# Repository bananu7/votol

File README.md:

# bananu7/Votol
Hello. This is my repository for all things related to the Votol controllers I was able to gather and put together.

## My use case and context

I'm converting a CRF250 MX motorcycle to electric power, using the Votol EM260SGTP controller. I want to have a bit more control over it that usual, so I decided to learn more about it.
Unless otherwise noted, all descriptions, labels etc. apply to _my specific controller_. Different models of the controller can differ; make sure you understand the cable functions
and model of yours.

## Project structure

* `desktop/` - early beginnings of a desktop app that were meant to replace the original desktop programmer
* `embassy/` - firmware of the display controller that goes on the bike and communicates with Votol EM
* `reference/` - technical details and descriptions of the controller protocol

## Log

### 2025-02-18

I did some more work on the miscellaneous features for the display. Got better frame decoding working, modularized things and importantly created a simulation mode that allows development without a controller connected (still on real hardware, though). I'm still not sure how I want to present all the available data or what peripherals to connect. Ideas list includes:

* all main controller parameters (works for now: battery voltage, temperatures)
* ride mode
* all controller errors in readable format
* temperature alerts
* speed based on the RPM counter
* trip computer: speed * time (distance traveled), current * time (amp-hours used), max/avg speed, max/avg current, moving time

Additional features based on peripheral hw:
* RTC - clock :), configuration (maybe I could use internal RTC)
* SD or flash - datalogger (trip computer but as series)
* IMU, magnetometer - compass, lean-aware TC
* front wheel speed sensor - TC, more accurate speed
* GPS - time, datalogging position
* BT - phone app, remote config and data reading

This is just a mental note to myself; it's unlikely I'll get to doing all of the above. Once I get the basic features working, I'll also upload the CAD files for the enclosure and print a prototype.

### 2025-02-13

I should've started this log immediately, but better late than never. I have already done quite a lot of work, but a lot still remains to be done.
Dealing with the controller can roughly be grouped into two categories:

1) Programming - setting up current and voltage limits, throttle rampup, engine phase config and hall config, as well as pin functions
2) Using - happens in the vehicle

#### Programming

Programming by itself is reasonably straighforward. I need to write more about the programming setup in the reference section, but in short,
the controller comes with a programming USB dongle. This dongle plugs into a two-pin port on the controller colored blue and orange. In my case,
the two-pin interface is a 1M CAN bus, xceived using TJA1050, connecting to an STM microcontroller, then exposed to USB via an USB-to-serial converter.

The controller also comes with a desktop app that looks like it was written with MFC. The app seems to have been made for older, smaller controllers,
and in fact doesn't even show the 260 on the list. To communicate, it opens a serial port at either 9600 or 115200 baud. There's also the CAN
switch that in my case needed to be... disabled. I believe that it's mostly a consequence of historical debt and reuse. The app originally
talked to the controller via serial; once they switched to CAN they were limited to 8-byte data frames, so they added the intermediate translator
chip to the dongle, so that the old app can still talk to the new controller. Incidentally I've noticed that the serial data going back to the app
is 24 bytes long, while the controller only responds with two can frames - so the translator chip must be doing some shuffling and filling in the 
blanks.

I have recorded some of the programming transactions, but haven't saved them. In order to properly reverse engineer the protocol, a whole
communication scheme needs to be observed and the parameters isolated. That being said, as the app seems to work fine for now, this is of low
priority. Perhaps one exciting possibility here would be to replace it with a web-based version talking serial over WebUSB. That would be a massive
usability boost, but getting all controllers working correctly could be a challenge.

#### Using the controller

Much more interesting is what happens during use. I don't want to use the dongle, and CAN is actually a great interface for the vehicle use.
The displays normally utilized with this controller use the separate LIN output, but I see zero reason to do that. CAN is more robust and offers
much more functionality.

The controller exposes a lot of frames on the bus, none of which I've decoded yet. There's been some mentions from SIA that they're their internal
protocol, but nothing concrete about it. I wouldd assume the usual parameters would be broadcasted continously, which would be great for display
purposes.

At the same time, when the desktop app wants live data from the controller, it sends a special query packet. The controller "responds" by sending
two frames containing the vitals; they are described in the reference folder. I was able to successfully read and decode those frames, and
that's the current state in the `embassy` folder; operating on an STM32F103C8 microcontroller, using its onboard CAN controller and TJA1050 
transceiver. On the other end, I plugged in a simple 8x8x4 LED matrix controlled by four MAX7219 chips in series, over SPI. Works great and 
the display of basic parameters has already been achieved.

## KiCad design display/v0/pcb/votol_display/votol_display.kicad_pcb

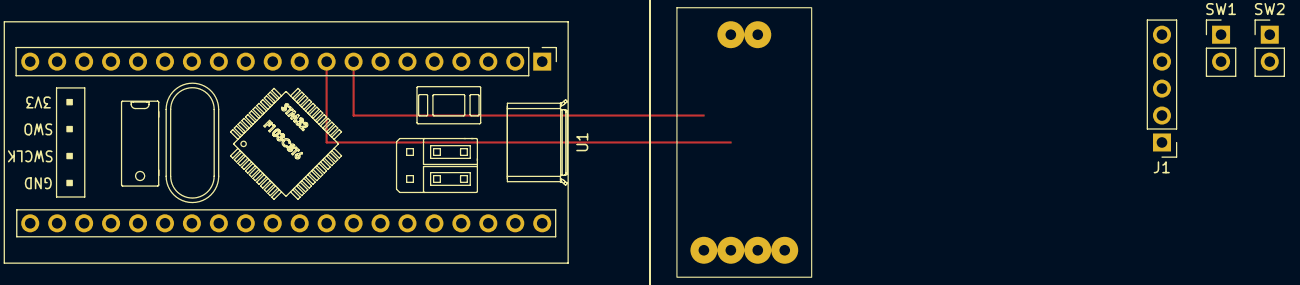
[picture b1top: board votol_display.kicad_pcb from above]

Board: 2 copper layers, 5 parts (0 on the bottom side), 6 nets, no tracks yet.

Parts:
J1: Conn_01x05_Pin; PinHeader_1x05_P2.54mm_Vertical
SW1, SW2: SW_Push; PinHeader_1x02_P2.54mm_Vertical
U1: YAAJ_BluePill; YAAJ_BluePill_1
U2: TJA_1050

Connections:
+5V: J1.1, U1.18 (5V), U2.3 (VCC)
CAN_PIN_RX: U1.8 (PA11), U2.5 (TX)
CAN_PIN_TX: U1.9 (PA12), U2.4 (RX)
GND: J1.5, SW1.2, SW2.2, U1.19 (GND), U1.39 (GND), U1.40 (GND), U2.6 (GND)
PIN_BUTTON_1: SW1.1, U1.35 (PB10)
PIN_BUTTON_2: SW2.1, U1.36 (PB11)

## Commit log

2025-02-01 Move app to proper folder
2025-02-01 Added more of the visualizer app
2025-02-01 Add rust implementation that simply polls the controller on the serial port
2025-02-06 Note dump
2025-02-06 Split up the desktop and embedded attempts
2025-02-06 Switched over to proper remote packages
2025-02-06 Added working SPI (bitbang for now) with max7219
2025-02-06 Added digits
2025-02-06 Small code reorg
2025-02-07 Added displaying whole numbers
2025-02-07 Made display init a util
2025-02-07 further librarized ledmatrix
2025-02-07 Working voltmeter
2025-02-07 Remove two unnecessary embassy examples
2025-02-07 Added voltage bar display at the botom
2025-02-07 Cleanup
2025-02-07 Cleaned up unsafe code by moving statics to main
2025-02-07 Cleaned up a couple warnings
2025-02-07 Remove dead code
2025-02-07 Add ledmatrix compositor
2025-02-07 Compositor works, shows both bar and voltage digits
2025-02-07 Added shift right feature
2025-02-07 Added blit
2025-02-07 Blitting now works
2025-02-18 Added more parameters
2025-02-18 Moved unused examples
2025-02-18 Add mocked frame
2025-02-18 Moved frame decoding to a separate module
2025-02-18 Add ARM target to rustup
2025-02-18 Disable CI tests for now
    There are none anyway
2025-02-18 More frame decoding functions
2025-02-18 Split off can communication to a submodule
2025-02-18 Added buttons and showing external temp
2025-02-18 Removed test x3 voltage multiplier
2025-02-19 Log 2025-02-18
2025-03-10 Moved can stuff to a separate submodule
2025-03-10 Preparing font storage for other characters
2025-03-10 Added all letters and output
2025-03-15 Fix letter N
2025-03-15 Remove unused import
2025-03-16 Added separate error screens
2025-03-20 Print current controller status on the right
2025-03-20 Refactor get_mode_char
2025-03-20 Added more params to display
2025-03-20 changed fullscreen float to accept negative values
2025-03-20 Added missing dash character
2025-03-20 Allow negative values for current and voltage
2025-03-20 Actually use motor temperature
2025-03-20 Add dot to fixed point decimals
2025-03-20 Display temperature grade sign
2025-03-21 Fixed write past bounds
2025-03-21 Better example frame
2025-03-21 fix fullscreen float
2025-03-21 Improved fullscreen numbers on ride screen
2025-03-22 Simple mode switch on button press - todo not all modes yet
2025-03-22 Restore fault screen
2025-03-22 Cycle through all modes
2025-03-22 Fix negative temps
2025-03-23 Pass explicit values to fake response
2025-03-23 Fix overflows
2025-03-23 Cleaned up all screens
2025-04-29 Add the screen electricals
2025-04-29 Change screen intensity to max
2025-05-28 Add controllerError enum
2025-05-28 Add writing controller error to screen
2025-05-28 Convert everything to lowercase
2025-05-28 Pass timer value to screens
2025-05-28 Remove unnecessary alloc::Format
2025-05-28 Remove unnecessary wait mode log
2025-05-28 Fix the error bytes location and add to test msg
2025-05-28 Add shift-left
2025-05-28 Scroll error text left
2025-05-28 Fixed error state messages and bytes
2025-05-28 Much nicer error state parsing and serialization
2025-07-26 very quick screen flip
2025-07-28 Improve comment
2025-07-28 Fix fake current, dont crash on negative nums
2025-07-28 Display power in kW
2025-07-28 Various fixes to number and voltage display
2025-07-28 Revert demo
